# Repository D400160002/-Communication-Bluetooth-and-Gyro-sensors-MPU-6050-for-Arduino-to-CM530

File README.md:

# -Communication-Bluetooth-and-Gyro-sensors-MPU-6050-for-Arduino-to-CM530
Merupakan Program Arduino yang berfungsi untuk mengontrol Robot Bioloid (CM-530) agar bisa menari atau bergerak dengan bluetooth dan keseimbangan dengan Gyro Sensors MPU 6050.

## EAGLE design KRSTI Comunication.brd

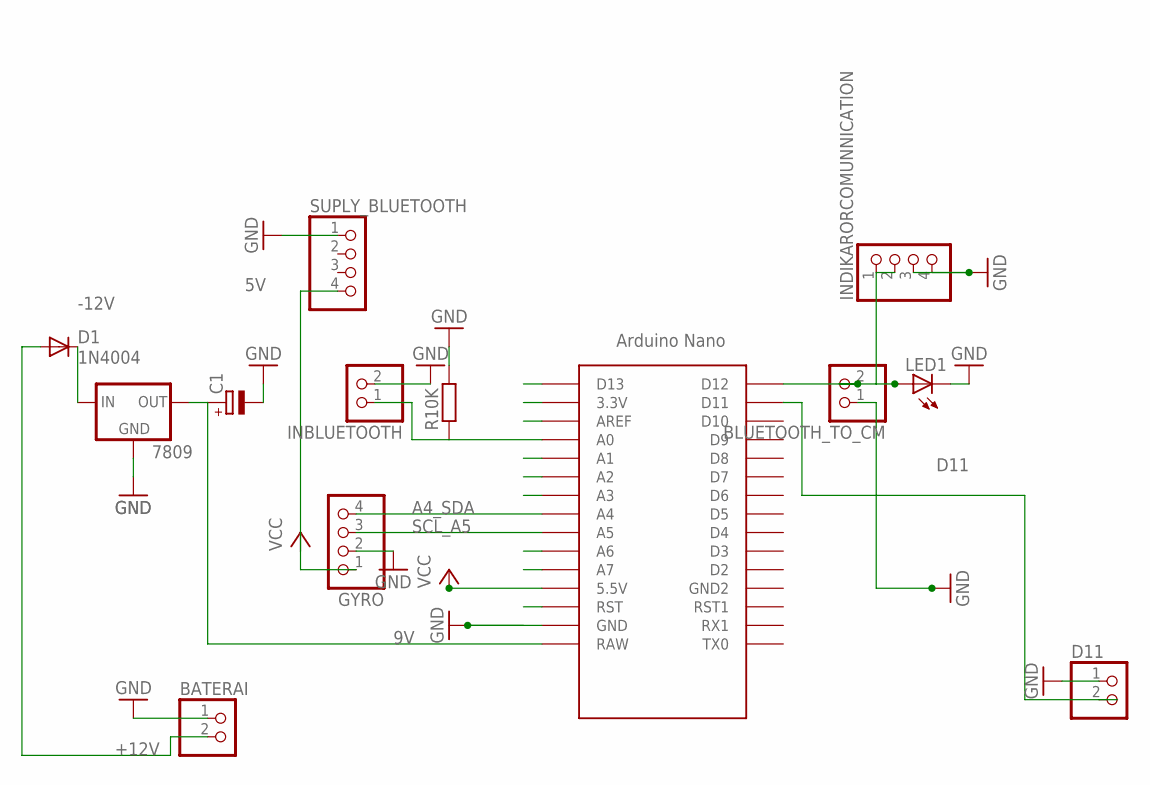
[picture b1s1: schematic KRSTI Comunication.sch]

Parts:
7809: 78XXL
BATERAI: PINHD-1X2/90; 1X02/90
BLUETOOTH_TO_CM: PINHD-1X2; 1X02
C1: CPOL-EUE2.5-5; E2,5-5
D1: 1N4004; DO41-10
D11: PINHD-1X2; 1X02
GYRO: PINHD-1X4; 1X04
INBLUETOOTH: PINHD-1X2; 1X02
INDIKARORCOMUNNICATION: PINHD-1X4/90; 1X04/90
LED1: LED5MM
R10K: R-EU_0207/7; 0207/7
SUPLY_BLUETOOTH: PINHD-1X4; 1X04
U$1: NANO

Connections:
3.3V: U$1.3.3V
5V: GYRO.1, SUPLY_BLUETOOTH.4, U$1.5V (5.5V)
9V: 7809.OUT, C1.+, U$1.RAW
+12V: BATERAI.2, D1.A
-12V: 7809.IN, D1.C
A0: INBLUETOOTH.1, R10K.1, U$1.A0
A1: U$1.A1
A2: U$1.A2
A3: U$1.A3
A4_SDA: GYRO.4, U$1.A4
A6: U$1.A6
A7: U$1.A7
D11: D11.2, U$1.D11
D12: BLUETOOTH_TO_CM.2, INDIKARORCOMUNNICATION.1, INDIKARORCOMUNNICATION.2, LED1.A, U$1.D12
D13: U$1.D13
GND: 7809.GND, BATERAI.1, BLUETOOTH_TO_CM.1, C1.-, D11.1, GYRO.2, INBLUETOOTH.2, INDIKARORCOMUNNICATION.3, INDIKARORCOMUNNICATION.4, LED1.K (C), R10K.2, SUPLY_BLUETOOTH.1, U$1.GND
RESET: U$1.RST
SCL_A5: GYRO.3, U$1.A5

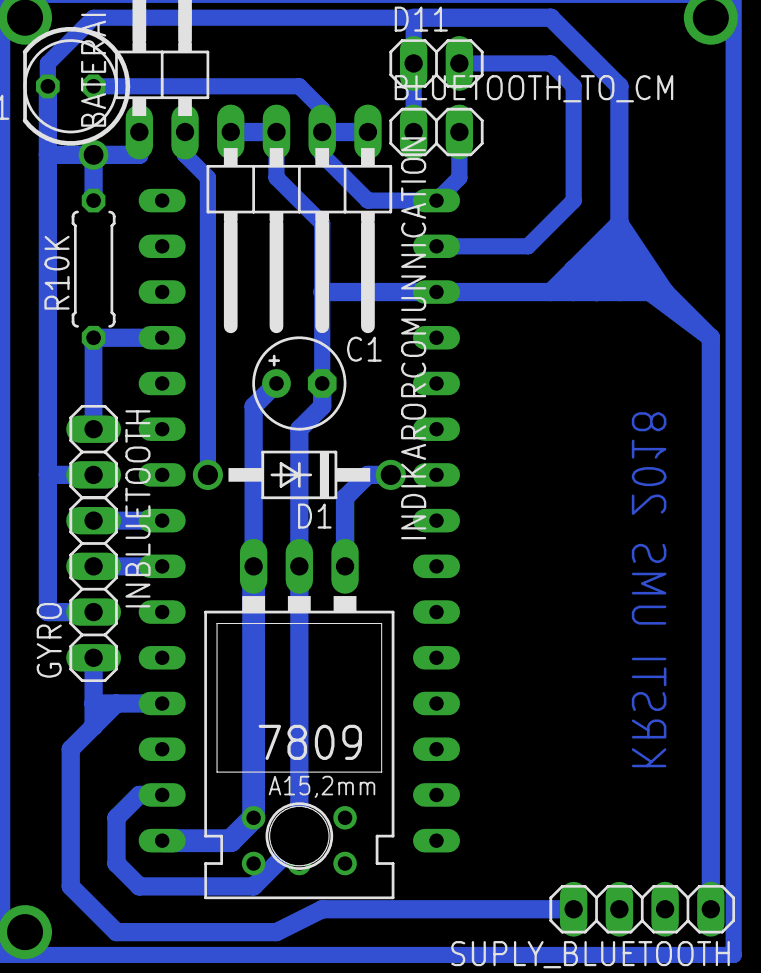
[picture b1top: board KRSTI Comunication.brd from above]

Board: 2 copper layers, 13 parts (0 on the bottom side), 10 nets.

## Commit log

2018-03-18 Code Arduino for bluetooth and Gyro sensor 6050.
2018-03-18 Schematic and Borad File Eagel
    Merupakan skematik untuk mengubugkan arduino ke CM 530.
2018-03-18 Datasheet For Arduino Nano
2018-03-18 Datasheet for CM-530
2018-03-18 Datasheet MPU 6050
